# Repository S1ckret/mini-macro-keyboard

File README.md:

# mini-macro-keyboard

View this project on [CADLAB.io](https://cadlab.io/project/23724). 

## Cloning

After cloning you need to configure (localy to repository) commit message template and init submodules. This will **NOT** override your global configuration.

```sh
git clone https://github.com/S1ckret/mini-macro-keyboard.git

cd mini-macro-keyboard

git config commit.template ./.git-commit-temlate

git submodule update --init
```

You are ready to work!

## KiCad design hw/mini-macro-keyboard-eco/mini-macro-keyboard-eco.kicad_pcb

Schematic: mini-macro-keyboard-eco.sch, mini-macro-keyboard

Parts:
C0, C1: 12p; C_0402_1005Metric
C2, C3, C7: 100n; C_0402_1005Metric
C4: 4.7u; C_0402_1005Metric
C5, C6: 1u; C_0402_1005Metric
D1, D2, D3: BLUE; LED_0603_1608Metric
H1, H2, H3, H4: MountingHole_Pad; MountingHole_2.2mm_M2_ISO7380_Pad
J0: USB; USB_Micro-B_Molex-105017-0001
J1: DEBUG_SWD; PinHeader_1x04_P2.54mm_Horizontal
R1, R2, R3: 330; R_0603_1608Metric
R5, R6: 10k; R_0402_1005Metric
SW1, SW2, SW3: SW_Cherry_MX_1.00u_PCB
SW5: LAYOUT; SW_SPDT_PCM12
SW6: BACKLIGHT; SW_SPDT_PCM12
U1: USBLC6-2SC6; SOT-23-6
U2: XC6206P322MR; SOT-23
U3: STM32F070F6P6; TSSOP-20_4.4x6.5mm_P0.65mm
Y1: 16 MHz; Crystal_SMD_3225-4Pin_3.2x2.5mm

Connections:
+3V3: C2.1, C3.1, C4.1, C6.1, C7.1, J1.1, SW5.1 (A), SW6.1 (A), U2.2 (VO), U3.5 (VDDA), U3.16 (VDD)
+5V: C5.1, J0.1 (VBUS), U1.5 (VBUS), U2.3 (VI)
GND: C0.1, C1.1, C2.2, C3.2, C4.2, C5.2, C6.2, C7.2, H1.1, H2.1, H3.1, H4.1, J0.4 (ID), J0.5 (GND), J1.4, R1.2, R2.2, R3.2, SW1.1, SW2.1, SW3.1, SW5.3 (C), SW6.3 (C), U1.2 (GND), U2.1 (GND), U3.1 (BOOT0), U3.15 (VSS), Y1.2, Y1.4
LED_1: D1.2 (A), U3.9 (PA3)
LED_2: D2.2 (A), U3.7 (PA1)
LED_3: D3.2 (A), U3.6 (PA0)
unnamed: D1.1 (K), R1.1
unnamed: D2.1 (K), R2.1
unnamed: D3.1 (K), R3.1
unnamed: R5.2, SW5.2 (B)
unnamed: R6.2, SW6.2 (B)
OSC_IN: C0.2, U3.2 (PF0), Y1.1
OSC_OUT: C1.2, U3.3 (PF1), Y1.3
SWCLK: J1.3, U3.20 (PA14)
SWDIO: J1.2, U3.19 (PA13)
SW_1: SW1.2, U3.13 (PA7)
SW_2: SW2.2, U3.12 (PA6)
SW_3: SW3.2, U3.11 (PA5)
SW_BACKLIGHT: R6.1, U3.10 (PA4)
SW_LAYOUT: R5.1, U3.14 (PB1)
USB_CONN_D+: J0.3 (D+), U1.3 (I/O2)
USB_CONN_D-: J0.2 (D-), U1.1 (I/O1)
USB_D+: U1.4 (I/O2), U3.18 (PA10/PA12)
USB_D-: U1.6 (I/O1), U3.17 (PA9/PA11)

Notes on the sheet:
Oscillator 16 MHz
USB 2.0 FS
Low dropout regulator (100 mA max)
STM32 Microcontroller
LEDs
Mechanical key switches
Debug SWD connector
Note: STM32F070F6P6 has internal D+ pull up resistor
Switches
Note: Each pin will have internal pull-up resistor
Mounting Holes

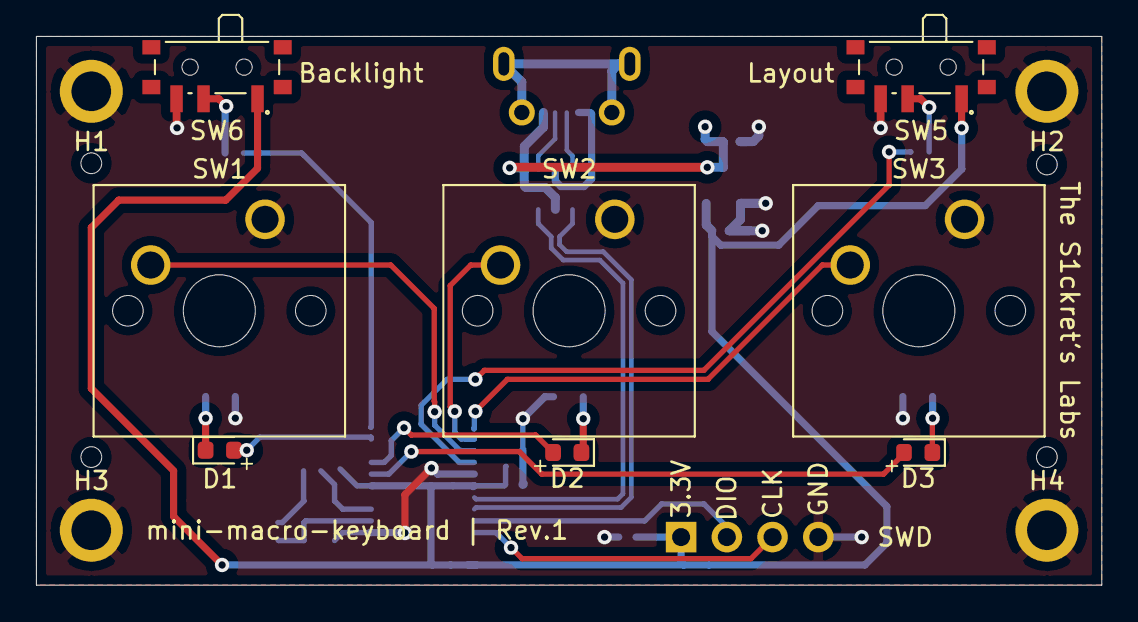
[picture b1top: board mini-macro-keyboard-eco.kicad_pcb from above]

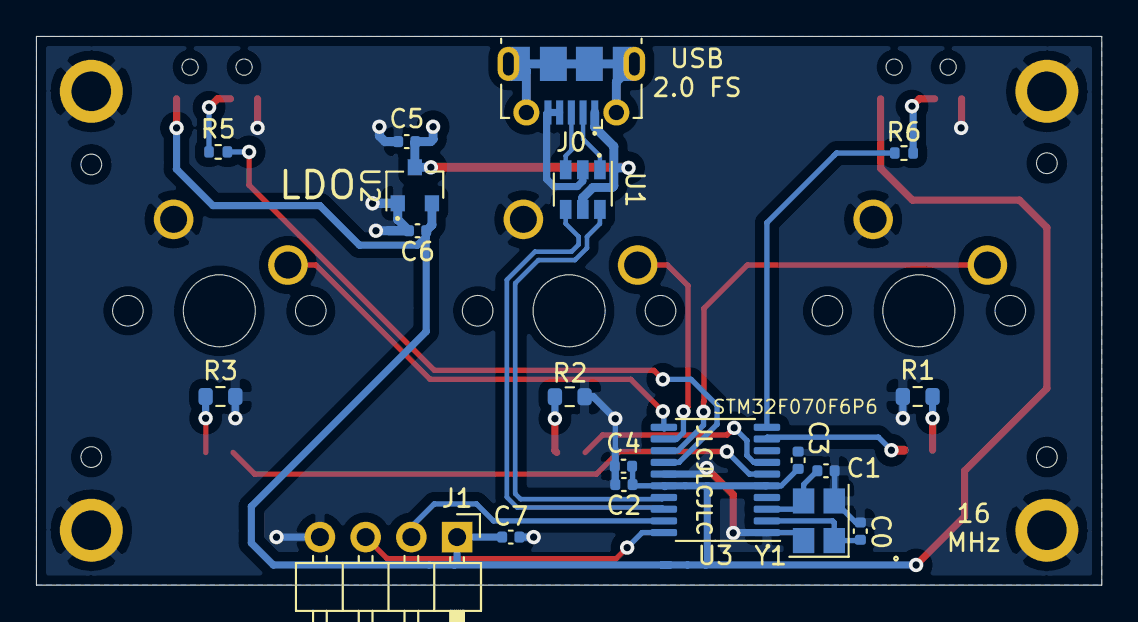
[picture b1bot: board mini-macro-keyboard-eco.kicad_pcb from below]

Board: 2 copper layers, 59.2 x 30.5 mm, 31 parts (19 on the bottom side), 24 nets.

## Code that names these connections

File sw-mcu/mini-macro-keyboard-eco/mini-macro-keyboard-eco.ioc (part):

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Mcu.Name=STM32F070F6Px
Mcu.Package=TSSOP20
Mcu.UserName=STM32F070F6Px
PA0.GPIOParameters=GPIO_Label
PA0.GPIO_Label=LED_3
PA0.Signal=GPIO_Output
PA1.GPIOParameters=GPIO_Label
PA1.GPIO_Label=LED_2
PA1.Signal=GPIO_Output
PA11.Mode=Device
PA11.Signal=USB_DM
PA12.Mode=Device
PA12.Signal=USB_DP
PA13.Mode=Serial_Wire
PA13.Signal=SYS_SWDIO
PA14.Mode=Serial_Wire
PA14.Signal=SYS_SWCLK
PA3.GPIOParameters=GPIO_Label
PA3.GPIO_Label=LED_1
PA3.Signal=GPIO_Output
PA4.GPIOParameters=GPIO_Label
PA4.GPIO_Label=SW_BACKLIGHT
PA4.Signal=GPXTI4
PA5.GPIOParameters=GPIO_Label
PA5.GPIO_Label=SW_3
PA5.Signal=GPXTI5
PA6.GPIOParameters=GPIO_Label
PA6.GPIO_Label=SW_2
PA6.Signal=GPXTI6
PA7.GPIOParameters=GPIO_Label
PA7.GPIO_Label=SW_1
PA7.Signal=GPXTI7
PB1.GPIOParameters=GPIO_Label
PB1.GPIO_Label=SW_LAYOUT
PB1.Signal=GPXTI1
PF0-OSC_IN.Mode=HSE-External-Oscillator
PF0-OSC_IN.Signal=RCC_OSC_IN
PF1-OSC_OUT.Mode=HSE-External-Oscillator
PF1-OSC_OUT.Signal=RCC_OSC_OUT
RCC.HSE_VALUE=16000000
RCC.SYSCLKFreq_VALUE=48000000
RCC.SYSCLKSource=RCC_SYSCLKSOURCE_PLLCLK
board=custom

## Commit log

2021-01-08 build(sw): add pinout
2021-01-08 feat(sw): add PoC
2021-01-08 chore(project): move project to the sw-mcu folder
2021-01-08 feat(hw): add kicad project
2021-01-08 Backlink to CADLAB.io has been added.
2021-01-09 chore(hw): add gitignore
2021-01-09 feat(hw): add stm32f103c8t6 to the schematic
2021-01-09 feat(hw): add boot0 switch
2021-01-09 feat(hw): add nrst switch
2021-01-09 feat(hw): add power supply
2021-01-09 feat(hw): add usblc6 protection
2021-01-09 feat(hw): add pin labels
2021-01-09 feat(hw): add crystal to the schematic
2021-01-09 fix(hw): remove VBAT connection
2021-01-09 fix(hw): add resitors after the usb protection
2021-01-09 feat(hw): add leds
2021-01-09 feat(hw): add buck dc/dc converter to the schematic
2021-01-09 feat(hw): add connector for st-link
2021-01-09 feat(hw): create library with mp2359 dc/dc buck
2021-01-09 fix(hw): replace spst to push button on the nrst line
2021-01-09 feat(hw): add switches
2021-01-09 style(hw): rename push switch
2021-01-09 style(hw): change label to power source
2021-01-10 style(hw): devide schematic into sections
2021-01-10 feat(hw): annotate schematic
2021-01-10 fix(hw): add ground to the buck converter
2021-01-10 style(hw): rename connector
2021-01-10 feat(hw): replace buck converter with ldo
2021-01-10 chore(hw): remove library with buck converter
2021-01-10 feat(hw): add project with stm32f070f6p6
    It is called eco, because it is economically better for my wallet
2021-01-20 feat: add commit message template
2021-01-20 chore(readme): add instruction to setup commit template
2021-01-20 feat!: add program body
    Uploaded a basic code of a program
2021-01-20 chore(hw): rescue eco schematic
    New version of the kicad is used
2021-01-20 feat(hw): assign footprints
2021-01-20 feat(hw): change design rules
2021-01-20 feat(hw): load netlist
2021-01-21 feat(hw): add rough layout
2021-01-21 style(hw): rename value fields
2021-01-21 fix(hw): remove debounce circuit from the mechanical switches
2021-01-21 feat(hw)!: remove reset push button
    BREAKING CHANGE:
    I remove the reset schematic becauce it uses a lot of space and
    I won't mess with usb bootloaders in the future. Also I don't know
    how to update software on the MCU in the user-friendly manner.
2021-01-21 feat(hw)!: remove boot switch
    I have removed boot switch because I don't expect to use another
    bootloaders
2021-01-21 feat(hw): reanotate schematic
2021-01-21 feat(hw): place components closer
2021-01-21 feat(hw): add mounting holes
2021-01-21 feat(hw): improve layout
2021-01-21 feat(hw): add edges
2021-01-21 feat(hw): move usb-b to the back layer
2021-01-22 feat(hw): add rooting
2021-01-22 feat(hw): add filled power and ground plates
2021-01-22 feat(hw): add silkscreen
2021-01-22 feat(hw): add cherry mx 3d model
2021-01-22 fix(hw): reroute some traces
2021-01-23 feat(sw-mcu): generate project
2021-02-03 feat(sw-mcu): add key driver
2021-02-03 feat(sw-mcu): add event core
2021-02-03 feat(sw-mcu): add backlight module
2021-02-03 feat(sw-mcu): add keyboard module
2021-02-03 feat(sw-mcu): add key module
2021-02-03 feat(sw-mcu): add list of modules
2021-02-03 feat(sw-mcu): link key and keyboard modules with events
2021-02-03 feat(sw-mcu): add hide report codec module
2021-02-03 feat(sw-mcu): add key press/release functions
2021-02-03 feat(sw-mcu): add init code
2021-02-03 feat(sw-mcu): add backlight interrupt processing
2021-02-03 feat(sw-mcu): add signals for hid codec
2021-02-03 feat(sw-mcu): add signals for keyboard
2021-02-03 fix(hw, #3): remove R0 resistor
2021-02-03 fix(hw, #4): remove 3.3v plate filling
2021-02-03 feat(hw): add jlcpcb parts number
2021-02-06 style(sw-mcu): rename drv_key to drv_switch
2021-02-06 feat(sw-mcu): add switches to the drv_switch
2021-02-06 chore(sw-mcu): add gitignore
2021-02-06 chore(sw-mcu): add build targets
2021-02-06 feat(sw-mcu): improve switch driver
2021-02-06 feat(sw-mcu): create flexible key module
2021-02-06 feat(sw-mcu): add protecrion from duplicated events
2021-02-06 style(sw-mcu): rename enum e_module_key to e_module_key_name
2021-02-06 feat(sw-mcu): add SYS_SIGNAL_NOP
2021-02-06 feat(sw-mcu): fix switch driver
2021-02-06 feat(sw-mcu): add e_timer_is_armed function
2021-02-06 feat(sw-mcu): add backlight switch module
2021-02-06 fix(sw-mcu): fix event forming in the key module
2021-02-06 feat(sw-mcu): add keys interrupt handling
2021-02-06 feat(sw-mcu): fix keys interrupt
2021-02-06 feat(sw-mcu): add switch modules
2021-02-06 feat(sw-mcu): add key switches
2021-02-06 feat(sw-mcu): add led toggle on key press
2021-02-06 feat(sw-mcu): handle interrupts for backlight switch
2021-02-07 feat(hid-sniffer): add git submodule
2021-02-07 chore(hid-sniffer): add readme
2021-02-07 chore: update readme
2021-02-07 feat(hid-sniffer): add test code
2021-02-08 feat(hid-sniffer): add basic CMakeLists
2021-02-10 feat(hid-sniffer): add search for mini-macro-keyboard
2021-02-10 feat(sw-mcu): add test descriptor
2021-02-10 feat(sw-mcu)!: add hardcoded report codec module
2021-02-10 chore(hid-sniffer): clean output
2021-02-12 feat(hid-sniffer): add report read/write
2021-02-12 feat(sw-mcu)!: add hardcoded report handling PoC
2021-02-14 Revert "feat(sw-mcu)!: add hardcoded report handling"
    This reverts commit 77f530ed609c5c58355a8f68c19c6d08ad203524.
2021-02-14 Revert "feat(sw-mcu)!: add hardcoded report codec module"
    This reverts commit a50b0d7ca3c17dbbea6203bb55fcfa5dec7573cc.
2021-02-14 Revert "feat(sw-mcu): add test descriptor"
    This reverts commit 54bbef4100349ad20f794b96760cfe77990b9ea8.
2021-02-14 feat(sw-mcu): add report descriptor
2021-02-14 feat(sw-mcu): add report passing to the report codec module
2021-02-14 feat(sw-mcu): add create macro command
2021-02-14 feat(sw-mcu): handle SIG_KEYBOARD_CREATE_MACRO
2021-02-15 feat(sw-mcu): add functions for key press/release in report codec module
2021-02-15 feat(sw-mcu): handle SIG_KEY_PRESSED / RELEASED in report codec module
2021-02-15 feat(sw-mcu): send event from keyboard to report_codec module
2021-02-15 feat(sw-mcu): init report_codec module
2021-02-20 fix(sw-mcu): fix report descriptor
    - vendor and keyboard parts are working simultaniously
2021-02-20 fix(sw-mcu): fix report id in SIG_KEY_RELEASE in report_codec
2021-02-20 feat(sw-mcu): add default test values for keyboard
2021-02-20 feat(sw-mcu): handle SIG_HID_CODEC_DATA_OUT in report_codec
2021-02-20 feat(sw-mcu): add led test indication
2021-02-20 feat(hid-sniffer): add create macro report
2021-02-21 feat(sw-mcu): parse byte1 for flags
2021-02-21 feat(hid-sniffer): add posibility to send custom reports
2021-02-21 refactor(sw-mcu): split code to functions in report codec module
2021-02-27 feat(hid-sniffer): fix device path to open
    TODO: automaticaly detect path
2021-02-27 feat(hid-sniffer): add exit command
2021-02-27 feat(sw-mcu): add variables check for create macro
    Add check to avoid array out of bound access
2021-02-27 feat(sw-mcu): implement SYNC command
    TODO: fix bug when syncing for the second time the key 0:2
    dissapears
2021-02-27 feat(sw-mcu): bump up timer quantity to 6
2021-02-27 feat(sw-mcu): assign default values for layout B
2021-02-27 feat(hid-sniffer): add reading for input SYNC reports
2021-02-27 chore(sw-mcu): move project to the mini-macro-keyboard folder
2021-03-02 feat(sw-mcu-eco): add project for STM32F070
2021-03-02 feat(sw-mcu-eco): move code to the STM32F070
2021-03-02 feat(sw-mcu-eco): correct code for STM32F070
2021-03-02 feat(sw-mcu-eco): add main init code for STM32F070
2021-03-02 feat(sw-mcu-eco): add build configurations
2021-03-02 feat(sw-mcu-eco): move report descriptor to the STM32F070
2021-03-02 feat(sw-mcu-eco): move interrupt related code to the STM32F070
2021-03-14 fix(sw-mcu-eco): fix backlight init
2021-03-14 fix(sw-mcu-eco): fix type table and timer
2021-03-14 fix(sw-mcu-eco): fix sending usb trash values
2021-03-14 feat(sw-mcu-eco): add layput switch
2021-03-14 feat(sw-mcu-eco): add layout switch
